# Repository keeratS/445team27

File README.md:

# 445team27
a repo to serve as a git-based lab notebook for the work of Team 27 in ECE 445

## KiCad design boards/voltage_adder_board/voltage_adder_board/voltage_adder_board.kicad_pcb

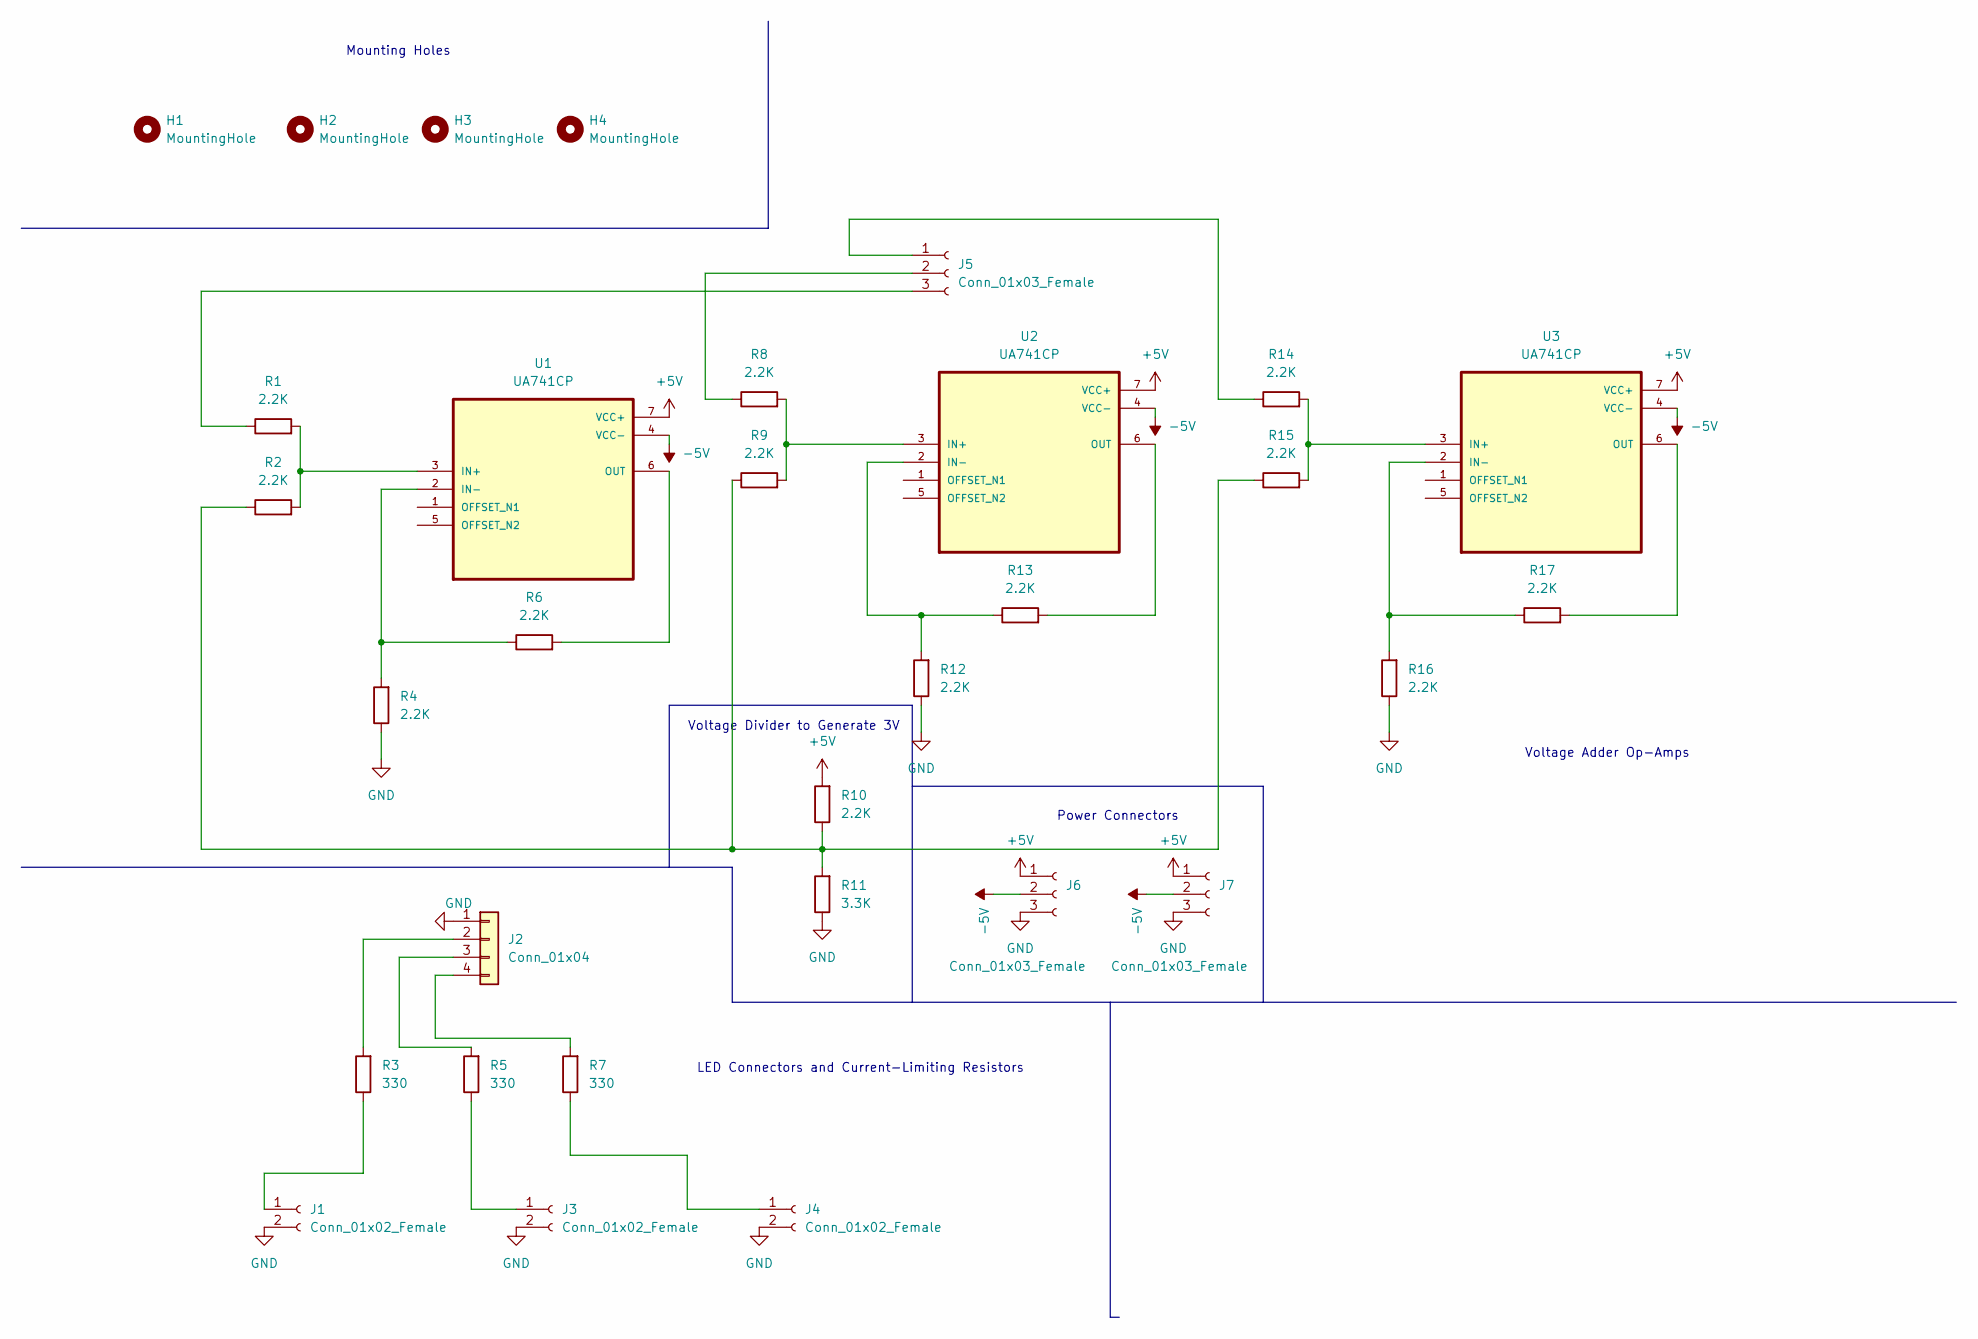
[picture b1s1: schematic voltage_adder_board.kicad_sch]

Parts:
H1, H2, H3, H4: MountingHole; MountingHole_3.2mm_M3
J1, J3, J4: Conn_01x02_Female; Molex_KK-254_AE-6410-02A_1x02_P2.54mm_Vertical
J2: Conn_01x04; Molex_KK-254_AE-6410-04A_1x04_P2.54mm_Vertical
J5, J6, J7: Conn_01x03_Female; Molex_KK-254_AE-6410-03A_1x03_P2.54mm_Vertical
R1, R2, R4, R6, R8, R9, R10, R12, R13, R14, R15, R16, R17: 2.2K; R_Axial_DIN0614_L14.3mm_D5.7mm_P15.24mm_Horizontal
R3, R5, R7: 330; R_Axial_DIN0614_L14.3mm_D5.7mm_P15.24mm_Horizontal
R11: 3.3K; R_Axial_DIN0614_L14.3mm_D5.7mm_P15.24mm_Horizontal
U1, U2, U3: UA741CP; DIP794W45P254L959H508Q8

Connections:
+5V: J6.1, J7.1, R10.2, U1.7 (VCC+), U2.7 (VCC+), U3.7 (VCC+)
-5V: J6.2, J7.2, U1.4 (VCC-), U2.4 (VCC-), U3.4 (VCC-)
GND: J1.2, J2.1, J3.2, J4.2, J6.3, J7.3, R4.1, R11.1, R12.1, R16.1
unnamed: J1.1, R3.1
unnamed: J2.2, R3.2
unnamed: J2.3, R5.2
unnamed: J2.4, R7.2
unnamed: J3.1, R5.1
unnamed: J4.1, R7.1
unnamed: J5.1, R14.1
unnamed: J5.2, R8.1
unnamed: J5.3, R1.1
unnamed: R1.2, R2.2, U1.3 (IN+)
unnamed: R4.2, R6.1, U1.2 (IN-)
unnamed: R6.2, U1.6 (OUT)
unnamed: R8.2, R9.2, U2.3 (IN+)
unnamed: R2.1, R9.1, R10.1, R11.2, R15.1
unnamed: R12.2, R13.1, U2.2 (IN-)
unnamed: R13.2, U2.6 (OUT)
unnamed: R14.2, R15.2, U3.3 (IN+)
unnamed: R16.2, R17.1, U3.2 (IN-)
unnamed: R17.2, U3.6 (OUT)

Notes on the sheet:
Voltage Adder Op-Amps
Power Connectors
Mounting Holes
Voltage Divider to Generate 3V
LED Connectors and Current-Limiting Resistors

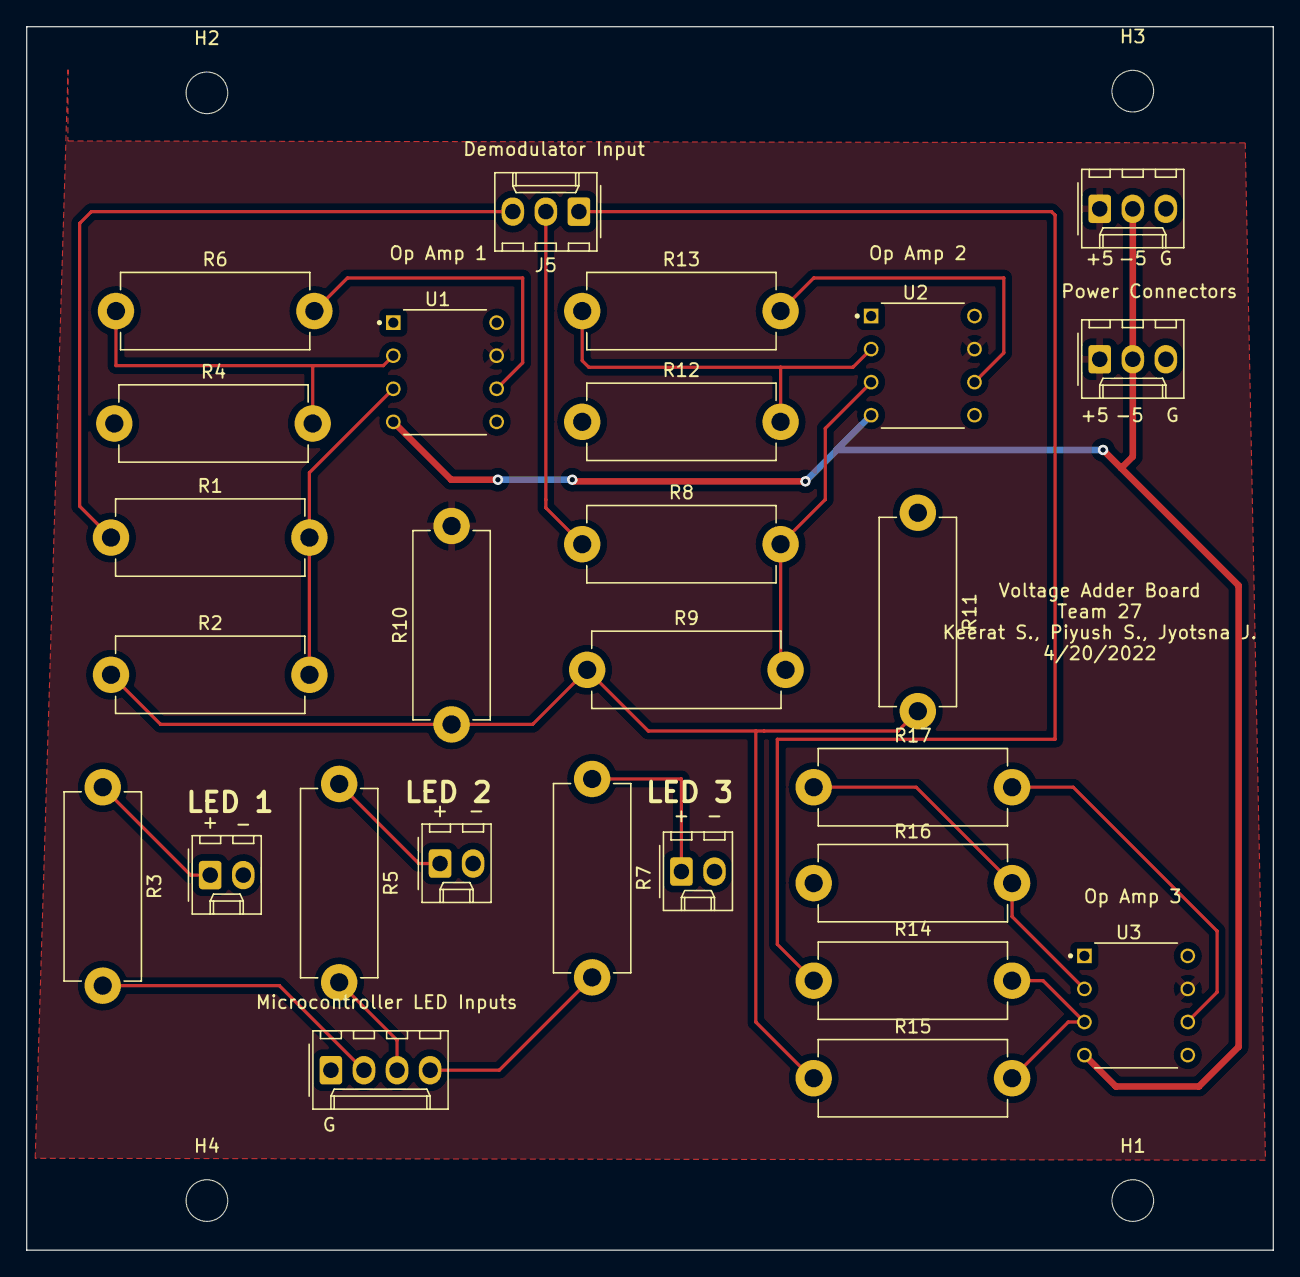
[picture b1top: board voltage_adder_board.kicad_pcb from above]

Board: 2 copper layers, 95.8 x 94.0 mm, 31 parts (0 on the bottom side), 22 nets.

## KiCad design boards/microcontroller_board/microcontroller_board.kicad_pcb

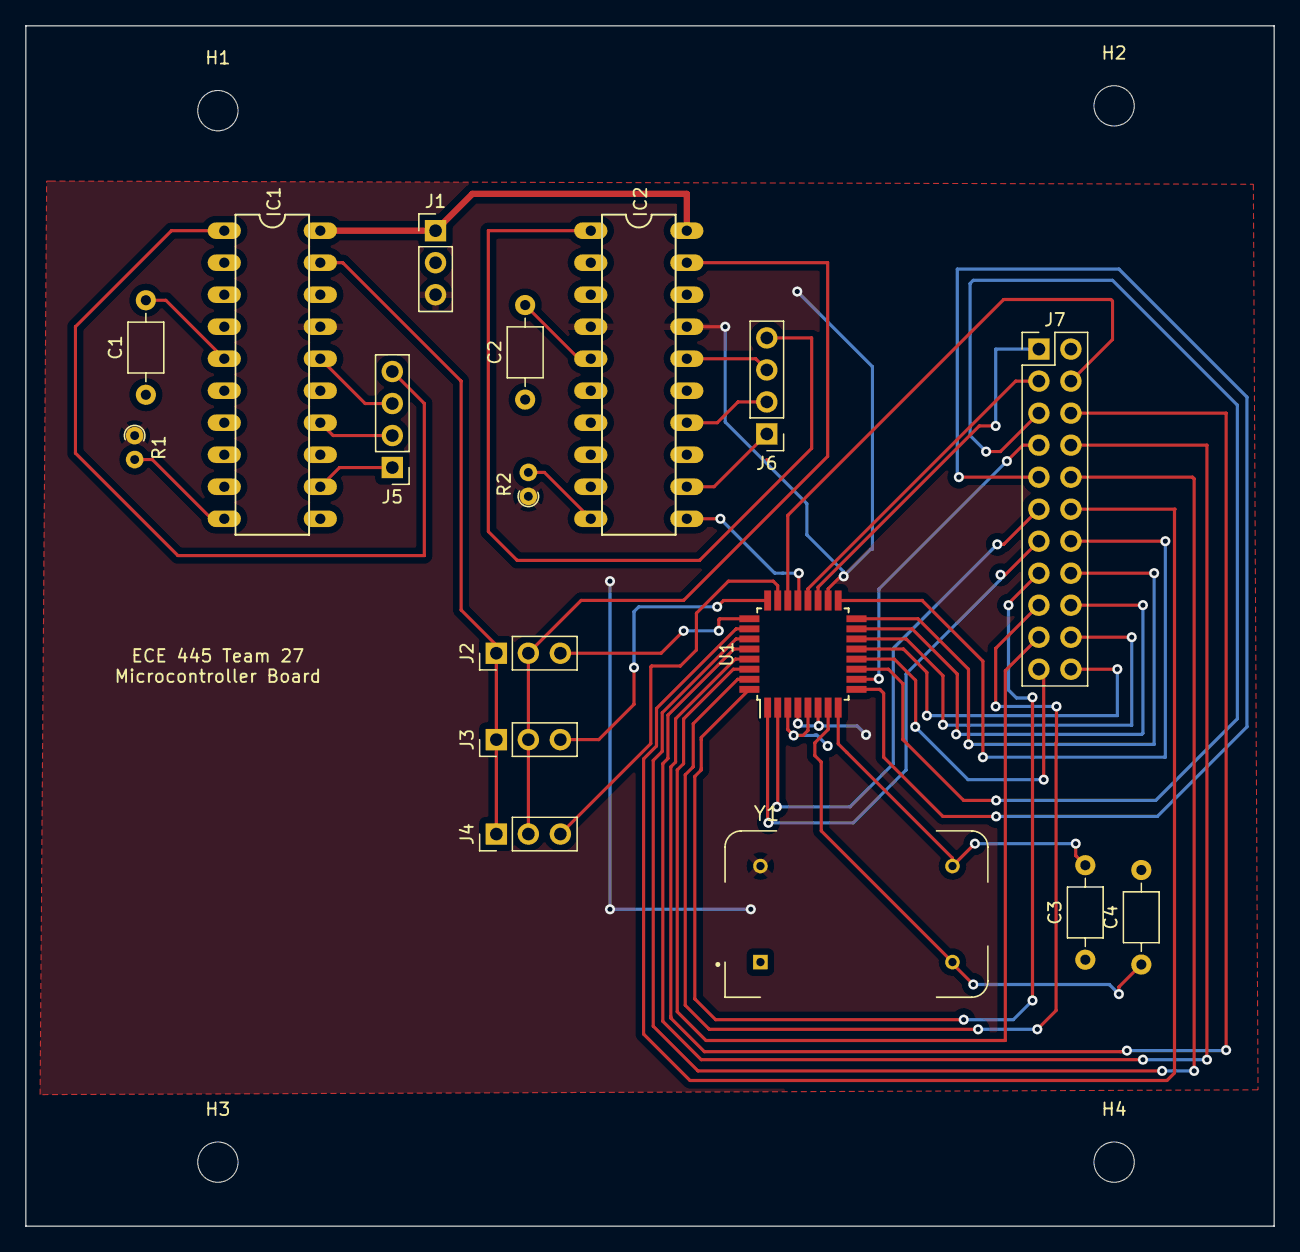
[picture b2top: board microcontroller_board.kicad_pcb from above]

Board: 2 copper layers, 99.1 x 95.2 mm, 21 parts (0 on the bottom side), 43 nets.

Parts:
C1, C2: 3300pF; C_Axial_L3.8mm_D2.6mm_P7.50mm_Horizontal
C3, C4: 22pF; C_Axial_L3.8mm_D2.6mm_P7.50mm_Horizontal
H1, H2, H3, H4: MountingHole; MountingHole_3.2mm_M3
IC1, IC2: MAX038*; DIL20
J1, J2, J3, J4: Conn_01x03_Male; PinHeader_1x03_P2.54mm_Vertical
J5, J6: Conn_01x04_Male; PinHeader_1x04_P2.54mm_Vertical
J7: Conn_02x11_Odd_Even; PinHeader_2x11_P2.54mm_Vertical
R1, R2: 49K; R_Axial_DIN0204_L3.6mm_D1.6mm_P1.90mm_Vertical
U1: ATmega328P-A; TQFP-32_7x7mm_P0.8mm
Y1: ECS-100AX-073; OSC_ECS-100AX-073

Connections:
+5V: IC1.17 (V+), IC2.4 (A1), IC2.17 (V+), J1.3, R1.1, R2.1, U1.4 (VCC), U1.6 (VCC), U1.18 (AVCC), Y1.14 (+VDC)
-5V: IC1.20 (V-), IC2.20 (V-), J1.1
GND: C1.1, C2.1, C3.1, C4.2, IC1.2, IC1.3 (A0), IC1.4 (A1), IC1.6, IC1.7 (DADJ), IC1.8 (FADJ), IC1.9, IC1.11, IC1.13 (PDI), IC1.15 (DGND), IC1.18, IC2.2, IC2.3 (A0), IC2.6, IC2.7 (DADJ), IC2.8 (FADJ), IC2.9, IC2.11, IC2.13 (PDI), IC2.15 (DGND), IC2.18, J1.2, U1.3 (GND), U1.5 (GND), U1.21 (GND)
unnamed: C1.2, IC1.5 (COSC)
unnamed: C2.2, IC2.5 (COSC)
unnamed: C3.2, U1.8 (XTAL2/PB7), Y1.8 (OUTPUT)
unnamed: C4.1, U1.7 (XTAL1/PB6), Y1.7 (CASE_GND)
unnamed: IC1.1 (REF), J5.4
unnamed: IC1.10 (IIN), R1.2
unnamed: IC1.12 (PDO), J5.1
unnamed: IC1.14 (SYNC), J5.2
unnamed: IC1.16 (DV+), J5.3
unnamed: IC1.19 (OUT), J2.1, J3.1, J4.1
unnamed: IC2.1 (REF), J6.4
unnamed: IC2.10 (IIN), R2.2
unnamed: IC2.12 (PDO), J6.1
unnamed: IC2.14 (SYNC), J6.2
unnamed: IC2.16 (DV+), J6.3
unnamed: IC2.19 (OUT), J2.2, J3.2, J4.2
unnamed: J2.3, U1.25 (PC2)
unnamed: J3.3, U1.24 (PC1)
unnamed: J4.3, U1.23 (PC0)
unnamed: J7.1, U1.19 (ADC6)
unnamed: J7.3, U1.20 (AREF)
unnamed: J7.4, U1.22 (ADC7)
unnamed: J7.5, U1.11 (PD7)
unnamed: J7.6, U1.29 (~RESET/PC6)
unnamed: J7.7, U1.10 (PD6)
unnamed: J7.8, U1.28 (PC5)
unnamed: J7.9, U1.9 (PD5)
unnamed: J7.10, U1.27 (PC4)
unnamed: J7.11, U1.2 (PD4)
unnamed: J7.12, U1.26 (PC3)
unnamed: J7.13, U1.1 (PD3)
unnamed: J7.14, U1.17 (PB5)
unnamed: J7.15, U1.32 (PD2)
unnamed: J7.16, U1.16 (PB4)
unnamed: J7.17, U1.31 (PD1)
unnamed: J7.18, U1.15 (PB3)
unnamed: J7.19, U1.30 (PD0)
unnamed: J7.20, U1.14 (PB2)
unnamed: J7.21, U1.12 (PB0)
unnamed: J7.22, U1.13 (PB1)

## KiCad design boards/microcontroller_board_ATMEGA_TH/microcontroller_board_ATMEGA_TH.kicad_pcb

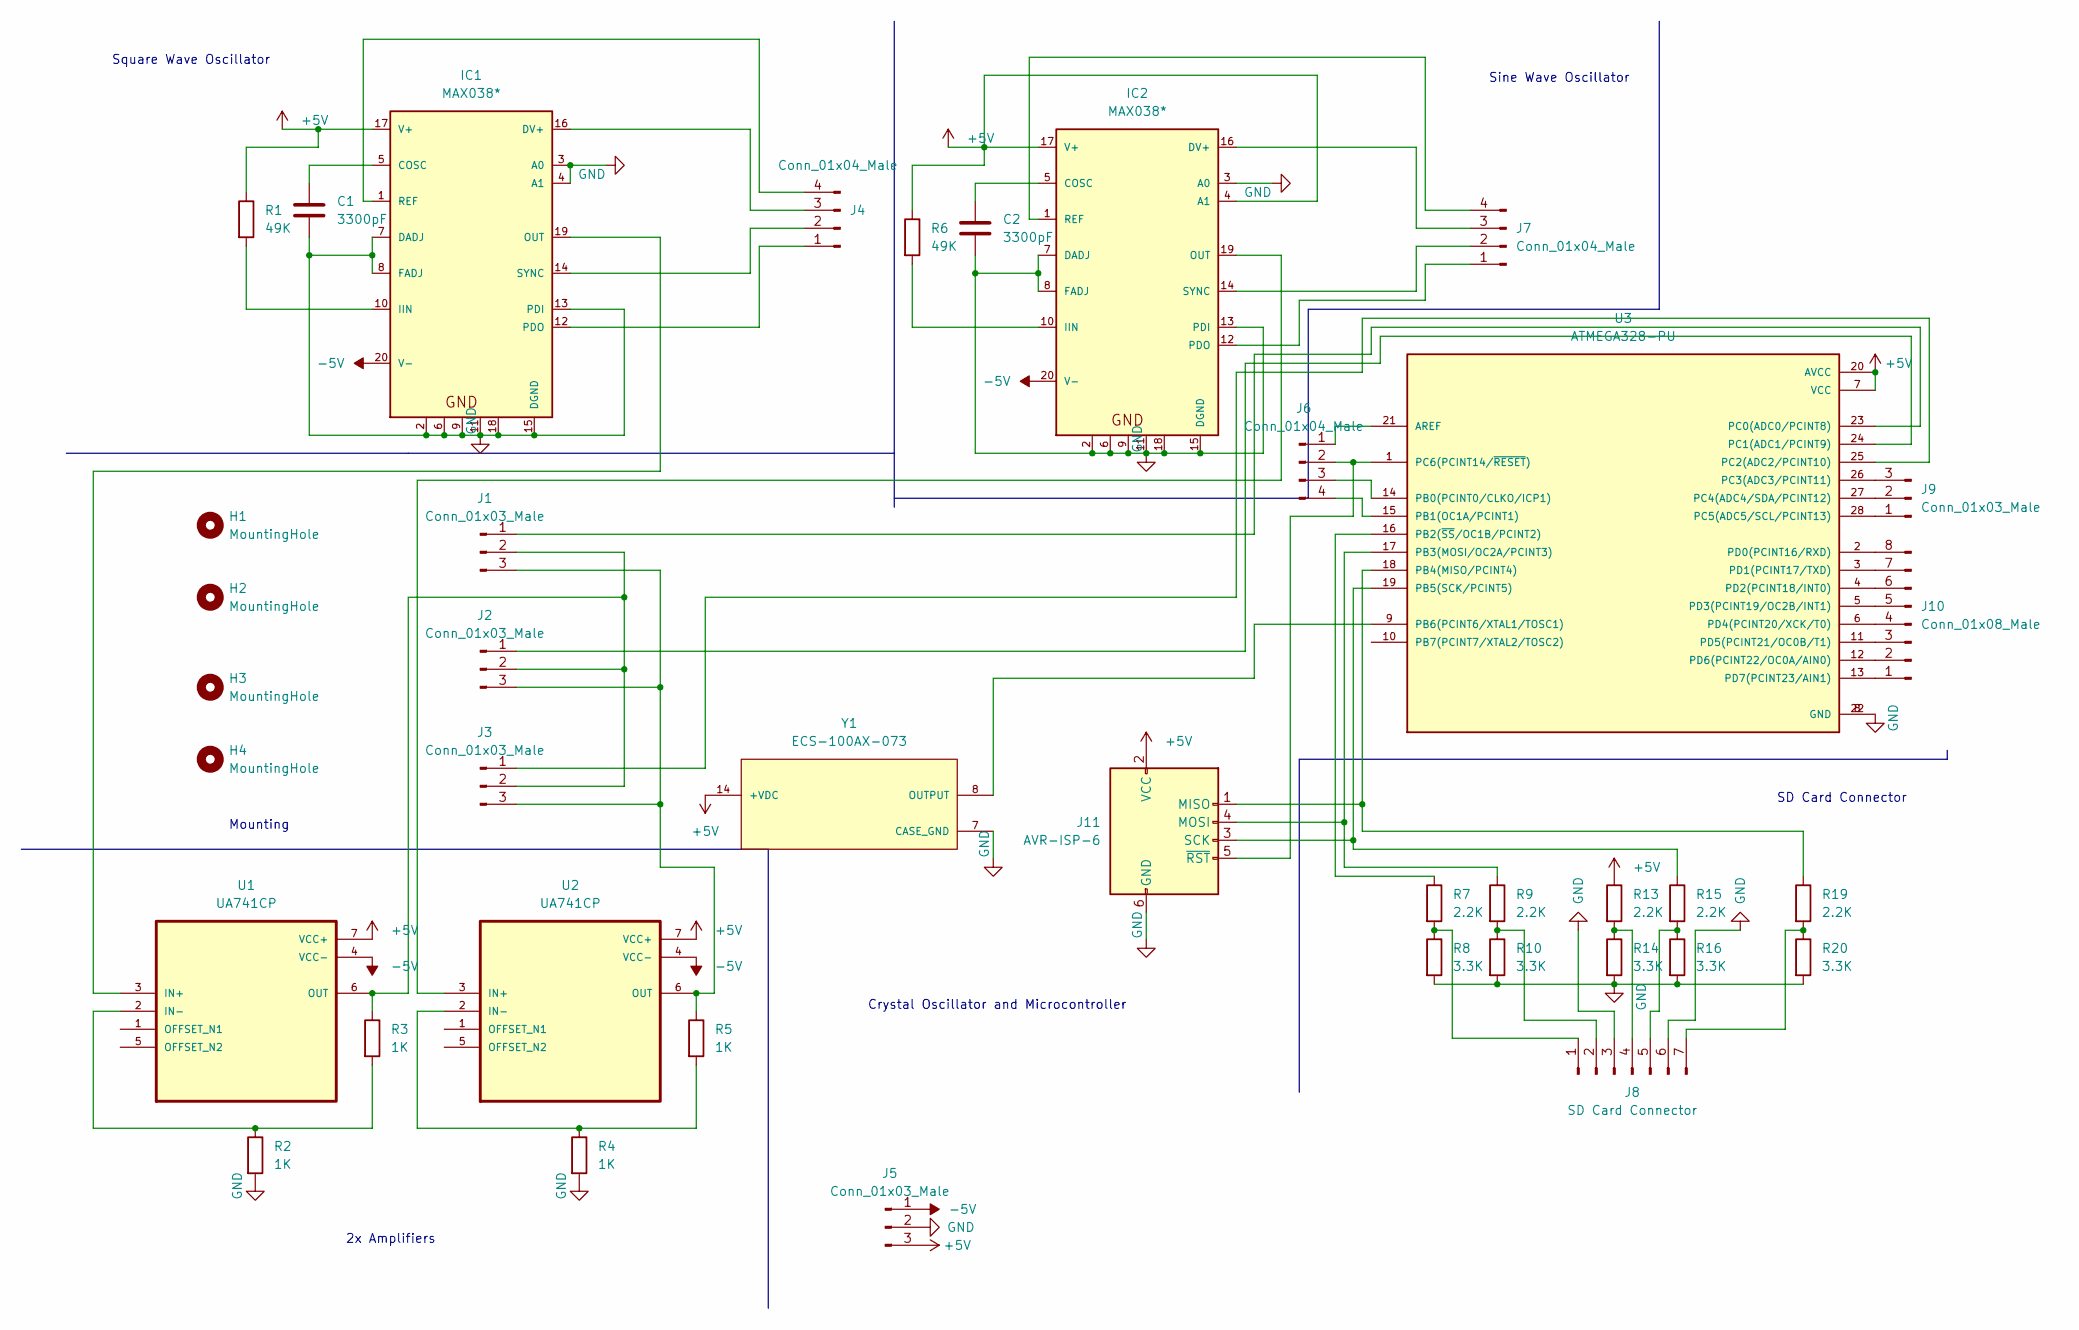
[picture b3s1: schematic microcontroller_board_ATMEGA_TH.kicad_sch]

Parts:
C1, C2: 3300pF; C_Axial_L3.8mm_D2.6mm_P7.50mm_Horizontal
H1, H2, H3, H4: MountingHole; MountingHole_3.2mm_M3
IC1, IC2: MAX038*; DIL20
J1, J2, J3, J5, J9: Conn_01x03_Male; PinHeader_1x03_P2.54mm_Vertical
J4, J6, J7: Conn_01x04_Male; PinHeader_1x04_P2.54mm_Vertical
J8: SD Card Connector; PinHeader_1x07_P2.54mm_Vertical
J10: Conn_01x08_Male; PinHeader_1x08_P2.54mm_Vertical
J11: AVR-ISP-6; IDC-Header_2x03_P2.54mm_Vertical
R1, R6: 49K; R_Axial_DIN0204_L3.6mm_D1.6mm_P1.90mm_Vertical
R2, R3, R4, R5: 1K; R_Axial_DIN0204_L3.6mm_D1.6mm_P1.90mm_Vertical
R7, R9, R13, R15, R19: 2.2K; R_Axial_DIN0204_L3.6mm_D1.6mm_P1.90mm_Vertical
R8, R10, R14, R16, R20: 3.3K; R_Axial_DIN0204_L3.6mm_D1.6mm_P1.90mm_Vertical
U1, U2: UA741CP; DIP794W45P254L959H508Q8
U3: ATMEGA328-PU; DIP787W46P254L3467H508Q28; PARTREV B
Y1: ECS-100AX-073; OSC_ECS-100AX-073

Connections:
+5V: IC1.17 (V+), IC2.4 (A1), IC2.17 (V+), J5.3, J11.2 (VCC), R1.1, R6.1, R13.1, U1.7 (VCC+), U2.7 (VCC+), U3.7 (VCC), U3.20 (AVCC), Y1.14 (+VDC)
-5V: IC1.20 (V-), IC2.20 (V-), J5.1, U1.4 (VCC-), U2.4 (VCC-)
GND: C1.1, C2.1, IC1.2, IC1.3 (A0), IC1.4 (A1), IC1.6, IC1.7 (DADJ), IC1.8 (FADJ), IC1.9, IC1.11, IC1.13 (PDI), IC1.15 (DGND), IC1.18, IC2.2, IC2.3 (A0), IC2.6, IC2.7 (DADJ), IC2.8 (FADJ), IC2.9, IC2.11, IC2.13 (PDI), IC2.15 (DGND), IC2.18, J5.2, J8.3, J8.6, J11.6 (GND), R2.2, R4.2, R8.2, R10.2, R14.2, R16.2, R20.2, U3.8 (GND), U3.22 (GND), Y1.7 (CASE_GND)
unnamed: C1.2, IC1.5 (COSC)
unnamed: C2.2, IC2.5 (COSC)
unnamed: IC1.1 (REF), J4.4
unnamed: IC1.10 (IIN), R1.2
unnamed: IC1.12 (PDO), J4.1
unnamed: IC1.14 (SYNC), J4.2
unnamed: IC1.16 (DV+), J4.3
unnamed: IC1.19 (OUT), U1.3 (IN+)
unnamed: IC2.1 (REF), J7.4
unnamed: IC2.10 (IIN), R6.2
unnamed: IC2.12 (PDO), J7.1
unnamed: IC2.14 (SYNC), J7.2
unnamed: IC2.16 (DV+), J7.3
unnamed: IC2.19 (OUT), U2.3 (IN+)
unnamed: J1.1, U3.23 (PC0(ADC0/PCINT8))
unnamed: J1.2, J2.2, J3.2, R3.1, U1.6 (OUT)
unnamed: J1.3, J2.3, J3.3, R5.1, U2.6 (OUT)
unnamed: J2.1, U3.24 (PC1(ADC1/PCINT9))
unnamed: J3.1, U3.25 (PC2(ADC2/PCINT10))
unnamed: J6.1, U3.21 (AREF)
unnamed: J6.2, J11.5 (~RST), U3.1 (PC6(PCINT14/~RESET))
unnamed: J6.3, U3.14 (PB0(PCINT0/CLKO/ICP1))
unnamed: J6.4, U3.15 (PB1(OC1A/PCINT1))
unnamed: J8.1, R7.2, R8.1
unnamed: J8.2, R9.2, R10.1
unnamed: J8.4, R13.2, R14.1
unnamed: J8.5, R15.2, R16.1
unnamed: J8.7, R19.2, R20.1
unnamed: J9.1, U3.28 (PC5(ADC5/SCL/PCINT13))
unnamed: J9.2, U3.27 (PC4(ADC4/SDA/PCINT12))
unnamed: J9.3, U3.26 (PC3(ADC3/PCINT11))
unnamed: J10.1, U3.13 (PD7(PCINT23/AIN1))
unnamed: J10.2, U3.12 (PD6(PCINT22/OC0A/AIN0))
unnamed: J10.3, U3.11 (PD5(PCINT21/OC0B/T1))
unnamed: J10.4, U3.6 (PD4(PCINT20/XCK/T0))
unnamed: J10.5, U3.5 (PD3(PCINT19/OC2B/INT1))
unnamed: J10.6, U3.4 (PD2(PCINT18/INT0))
unnamed: J10.7, U3.3 (PD1(PCINT17/TXD))
unnamed: J10.8, U3.2 (PD0(PCINT16/RXD))
unnamed: R2.1, R3.2, U1.2 (IN-)
unnamed: R4.1, R5.2, U2.2 (IN-)
unnamed: R7.1, U3.16 (PB2(~SS/OC1B/PCINT2))
unnamed: J11.4 (MOSI), R9.1, U3.17 (PB3(MOSI/OC2A/PCINT3))
unnamed: J11.3 (SCK), R15.1, U3.19 (PB5(SCK/PCINT5))
unnamed: J11.1 (MISO), R19.1, U3.18 (PB4(MISO/PCINT4))
unnamed: U3.9 (PB6(PCINT6/XTAL1/TOSC1)), Y1.8 (OUTPUT)

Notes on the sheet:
2x Amplifiers
Sine Wave Oscillator
Square Wave Oscillator
Crystal Oscillator and Microcontroller
Mounting
SD Card Connector

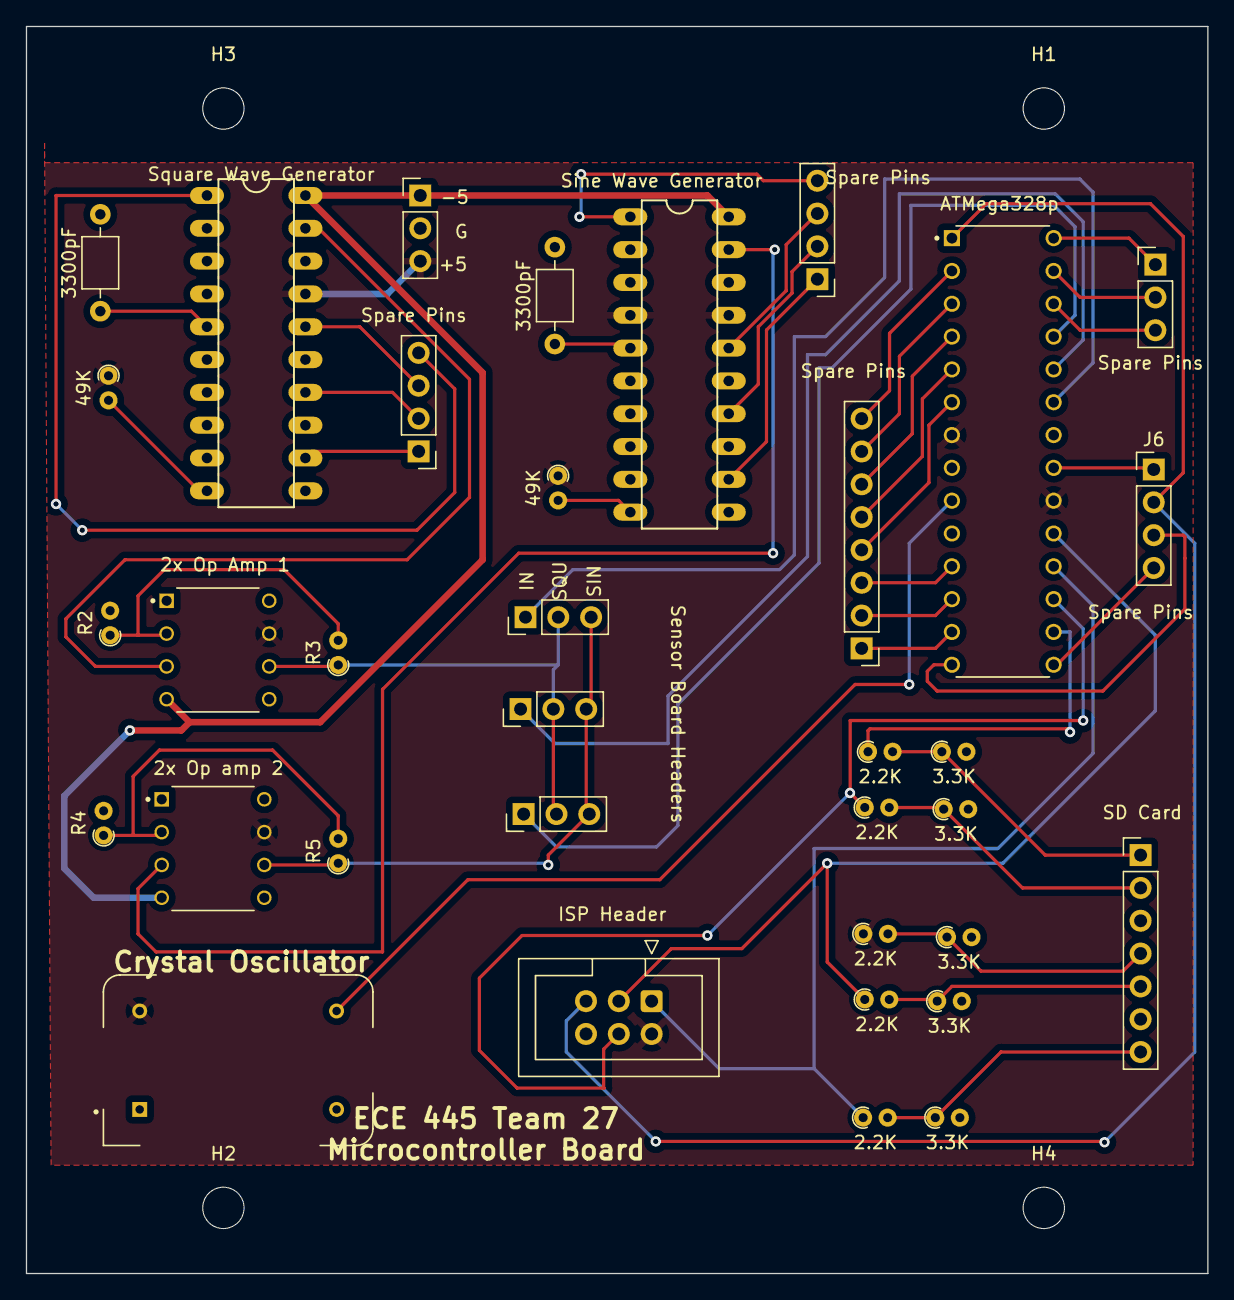
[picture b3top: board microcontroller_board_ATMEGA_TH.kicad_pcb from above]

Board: 2 copper layers, 91.4 x 96.5 mm, 39 parts (0 on the bottom side), 49 nets.

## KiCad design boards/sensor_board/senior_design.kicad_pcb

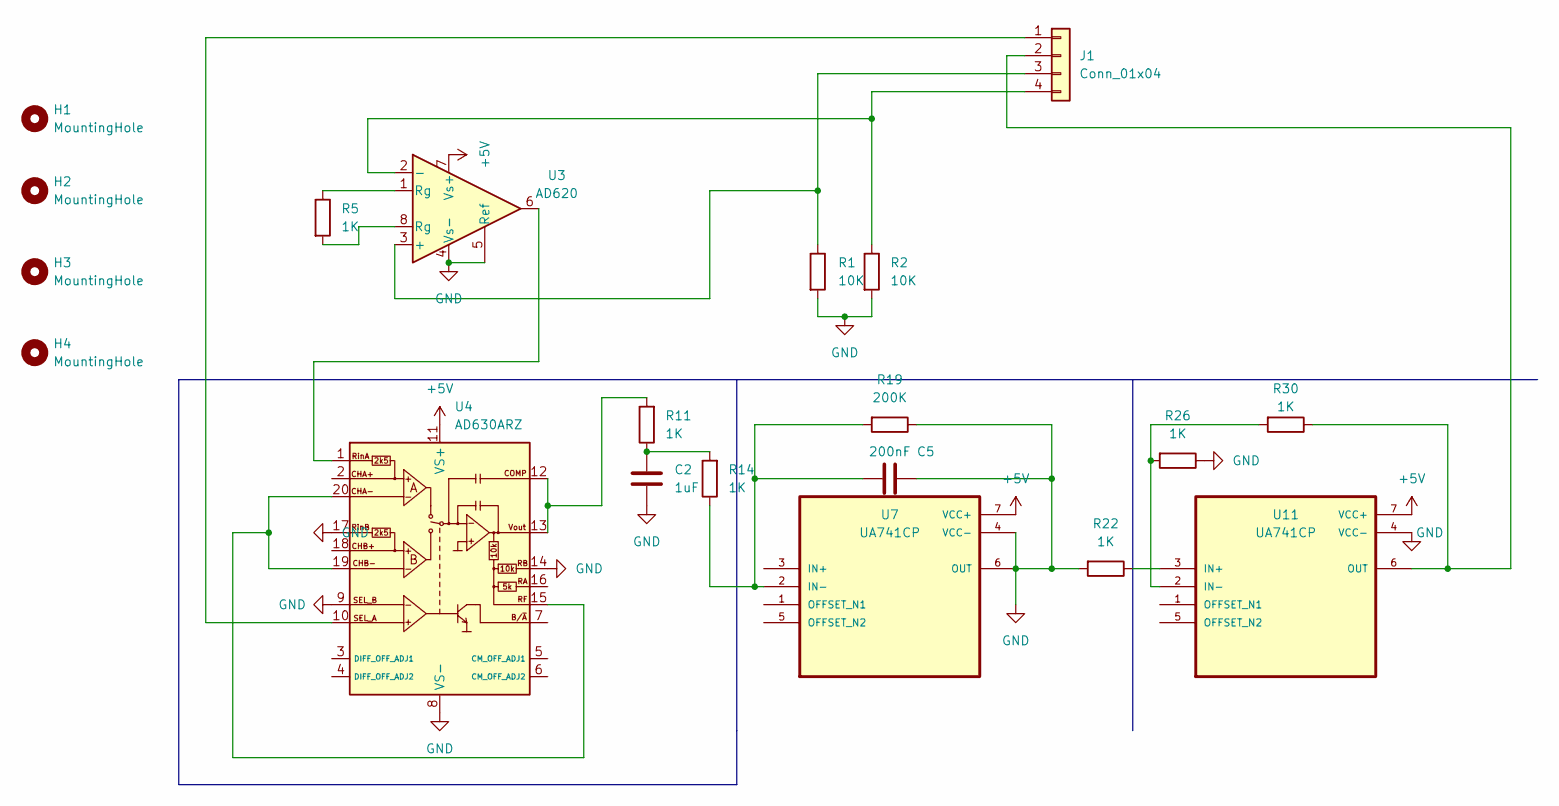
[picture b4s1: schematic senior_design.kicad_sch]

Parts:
C2: 1uF; C_0805_2012Metric_Pad1.18x1.45mm_HandSolder
C5: 200nF; C_0805_2012Metric_Pad1.18x1.45mm_HandSolder
H1, H2, H3, H4: MountingHole; MountingHole_3.2mm_M3
J1: Conn_01x04; Molex_KK-254_AE-6410-04A_1x04_P2.54mm_Vertical
R1, R2: 10K; R_0805_2012Metric_Pad1.20x1.40mm_HandSolder
R5, R11, R14, R22, R26, R30: 1K; R_0805_2012Metric_Pad1.20x1.40mm_HandSolder
R19: 200K; R_0805_2012Metric_Pad1.20x1.40mm_HandSolder
U3: AD620; DIL08
U4: AD630ARZ; SOIC-20W_7.5x12.8mm_P1.27mm
U7, U11: UA741CP; DIP794W45P254L959H508Q8

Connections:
+5V: U3.7 (Vs+), U4.11 (VS+), U7.7 (VCC+), U11.7 (VCC+)
GND: C2.1, C5.1, R1.2, R2.2, R19.1, R22.2, R26.1, U3.4 (Vs-), U3.5 (Ref), U4.8 (VS-), U4.9 (SEL_B), U4.14 (RB), U4.17 (RinB), U7.4 (VCC-), U7.6 (OUT), U11.4 (VCC-)
unnamed: C2.2, R11.1, R14.2
unnamed: C5.2, R14.1, R19.2, U7.2 (IN-)
unnamed: J1.2, R30.1, U11.6 (OUT)
unnamed: J1.3, R1.1, U3.3 (+)
unnamed: J1.4, R2.1, U3.2 (-)
unnamed: R5.1, U3.1 (Rg)
unnamed: R5.2, U3.8 (Rg)
unnamed: R11.2, U4.12 (COMP), U4.13 (Vout)
unnamed: R22.1, U11.3 (IN+)
unnamed: R26.2, R30.2, U11.2 (IN-)
unnamed: U3.6, U4.1 (RinA)
unnamed: J1.1, U4.10 (SEL_A)
unnamed: U4.15 (RF), U4.19 (CHB-), U4.20 (CHA-)

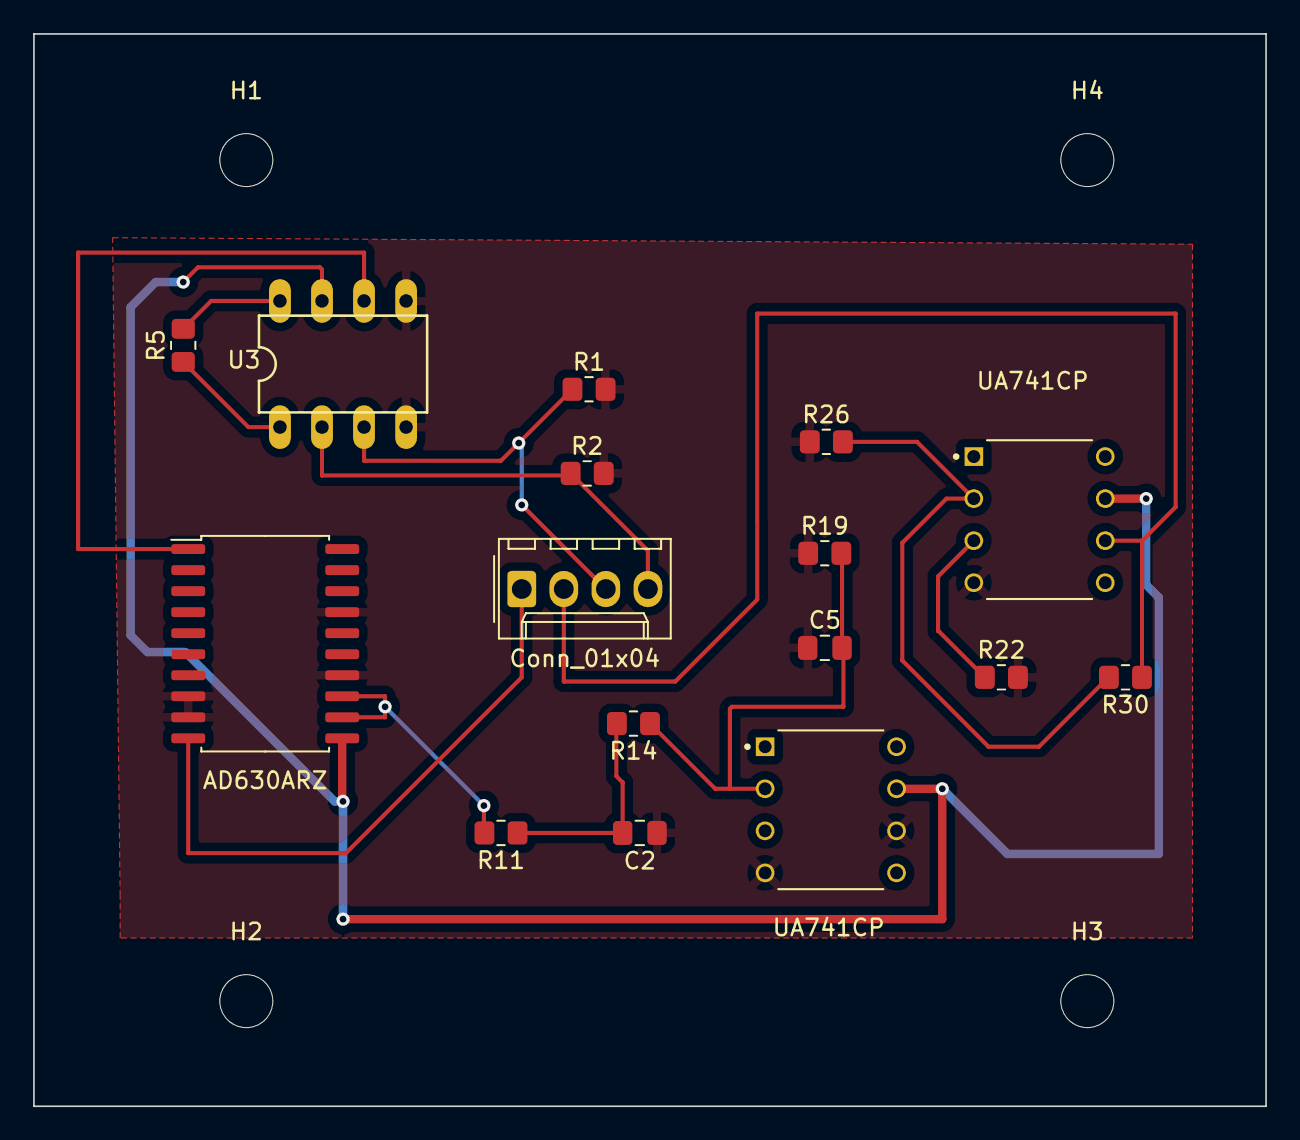
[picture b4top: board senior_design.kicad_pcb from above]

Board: 2 copper layers, 74.4 x 64.8 mm, 20 parts (0 on the bottom side), 15 nets.

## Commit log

2022-02-06 added suggested structure
2022-02-09 updated keerat's notebook with progress from 2/8
2022-02-10 pictures of CAD 2/10
2022-02-10 now the pictures are formatted reasonably
2022-02-10 now the files are formatted correctly
2022-02-10 updated w images of house CAD
2022-02-15 update with project changes discussed with TA today
2022-02-17 Create TestFile
    jut checking i can make changes
2022-02-20 added info about prototype circuit and data collection from 2/19
2022-02-21 adding graph of data (from python code) for use in design document
2022-02-21 Create Dialectric Material Research
    base structure of dielectric constant research, not complete
2022-02-21 Update Dialectric Material Research
    figures on capacitance updated ; materials list required still
2022-02-21 Update Dialectric Material Research
    all figures updated, conclusion drawn, current simulation material recommendation stated
2022-02-21 updated pi lab notebook
2022-02-22 added info about new data collection
2022-02-22 updated to most recent data
2022-02-24 adding CAD drawings with dimensions
2022-02-24 adding new graph per Amr's request
2022-02-28 updated Keerat's notebook for the past week
2022-02-28 updated lab notebook
2022-03-01 updates for today
2022-03-04 started schematic and PCB
2022-03-04 added balanced demodulator to schematic
2022-03-07 updated page with lab measurements from earlier. will graph them soon
2022-03-07 adding plot
2022-03-07 added graph
2022-03-07 finished schematic
2022-03-08 added footprints, fixed error in schematic, started PCB layout
2022-03-08 changed schematic for 4 boards instead of 1
2022-03-08 updated with Sunday's lab work
2022-03-08 finished PCB for sensor board
2022-03-08 updated schematic text
2022-03-08 added VCC plane and generated gerber file
2022-03-22 added lab graph from break
2022-03-22 adding lab work graph from break work
2022-03-22 undoing accidental overwrite of PCB stuff
2022-03-22 Revert "adding lab work graph from break work"
    This reverts commit ef045a0d1219dc02987ec9d1b732cdd7fe4ee6f2.
2022-03-22 Revert "Merge branch 'main' of github.com:keeratS/445team27 into main"
    This reverts commit 777689c8a8ad57f7277eda5b46fe19858a00a95d, reversing
    changes made to 7e022650be9491f24625faac10ecfe32b749daf8.
    undoing mistaken merge
2022-03-23 oops in the merge and merge fix this got changed, i went in to the history and fixed the unintentional change, sorry!
2022-03-23 fixed markdown formatting
2022-03-23 added Amr meeting to notebook
2022-03-23 merging local changes
2022-03-23 added to lab notebook
2022-03-23 lab initial updates
2022-03-29 finished microcontroller board
2022-04-07 making sure I pushed everything
2022-04-07 SD card code + notebook update
2022-04-08 Create Lab Work Documentation
    the daily work in lab , documented
2022-04-12 Update Lab Work Documentation
    April 10 power supply work updated
2022-04-12 added to Keerat's lab notebook
2022-04-12 Update Lab Work Documentation
2022-04-18 added lab pictures 4/17
2022-04-18 Update README.md
    updated lab notebook with work from past few days
2022-04-18 Update README.md
    fixed formatting
2022-04-19 adding lab pic
2022-04-19 updating lab notebook
2022-04-19 lab picture
2022-04-19 update lab notebook
2022-04-19 added lab picture
2022-04-19 lab notesbook update
2022-04-19 lab update
2022-04-20 updated notebook
2022-04-20 lab updates 4/20
2022-04-20 voltage adder board
2022-04-21 finished voltage adder board
2022-04-21 gerber files
2022-04-25 lab updates
2022-04-25 fixed demo date
2022-04-25 added details about friday lab visit
2022-04-25 added code for arduino tube readings and writing on SD card
2022-04-25 lab updates.
2022-04-25 added new code with comments
2022-04-25 finished visualization code
2022-04-25 added lab updates
2022-04-26 fix to display code
2022-04-28 lab work updates
2022-05-01 oops I forgot to push this yesterday, It's the code that identifies interesting bee behavior times
2022-05-04 added details about python script
2022-05-05 added images for notebook
2022-05-05 uploading block diagram
